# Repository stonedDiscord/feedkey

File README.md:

Replacement PCB for the Zebra GK420 label printers.

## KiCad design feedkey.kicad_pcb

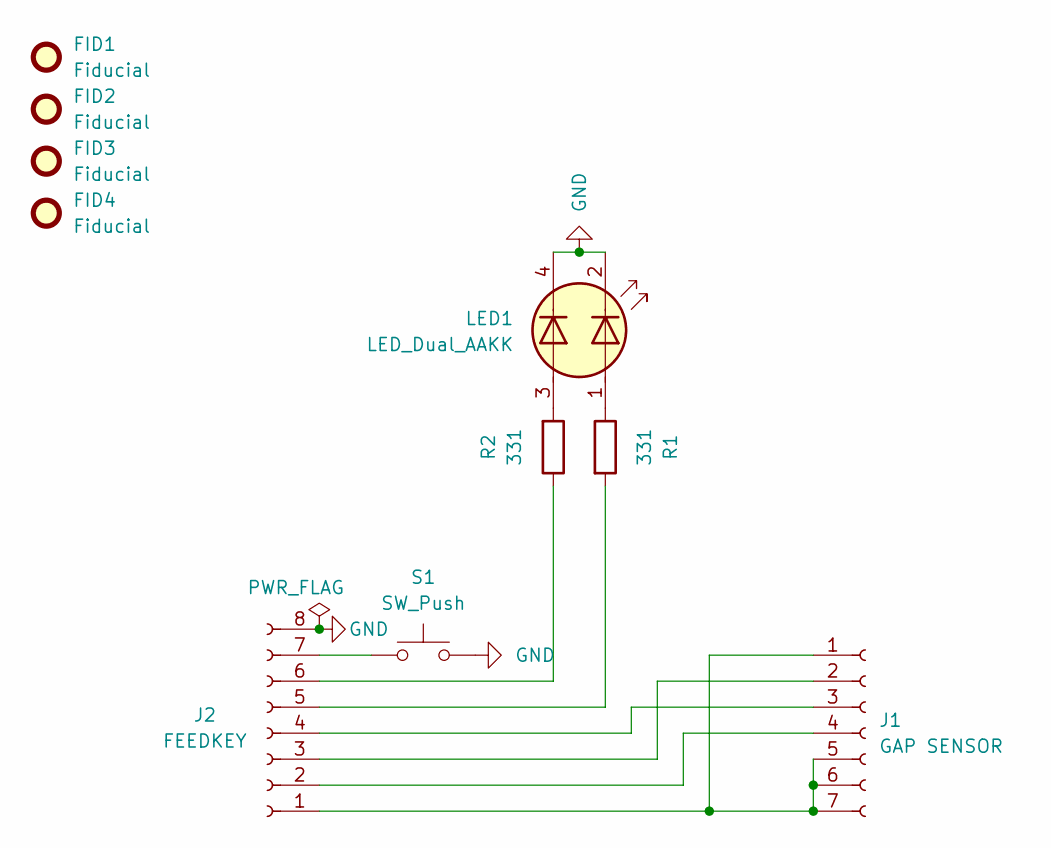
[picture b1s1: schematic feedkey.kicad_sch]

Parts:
FID1, FID2, FID3, FID4: Fiducial; Fiducial_1.5mm_Mask3mm
J1: GAP SENSOR; JST_GH_BM07B-GHS-TBT_1x07-1MP_P1.25mm_Vertical
J2: FEEDKEY; JST_GH_BM08B-GHS-TBT_1x08-1MP_P1.25mm_Vertical
LED1: LED_Dual_AAKK; LED_Kingbright_KPBD-3224
R1, R2: 331; LED_0805_2012Metric
S1: SW_Push; SW_Push_1P1T_NO_6x6mm_H9.5mm

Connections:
GND: J2.8, LED1.2 (K1), LED1.4 (K2), S1.2
unnamed: J1.1, J1.5, J1.6, J1.7, J2.1
unnamed: J1.2, J2.3
unnamed: J1.3, J2.4
unnamed: J1.4, J2.2
unnamed: J2.5, R1.2
unnamed: J2.6, R2.1
unnamed: J2.7, S1.1
unnamed: LED1.1 (A1), R1.1
unnamed: LED1.3 (A2), R2.2

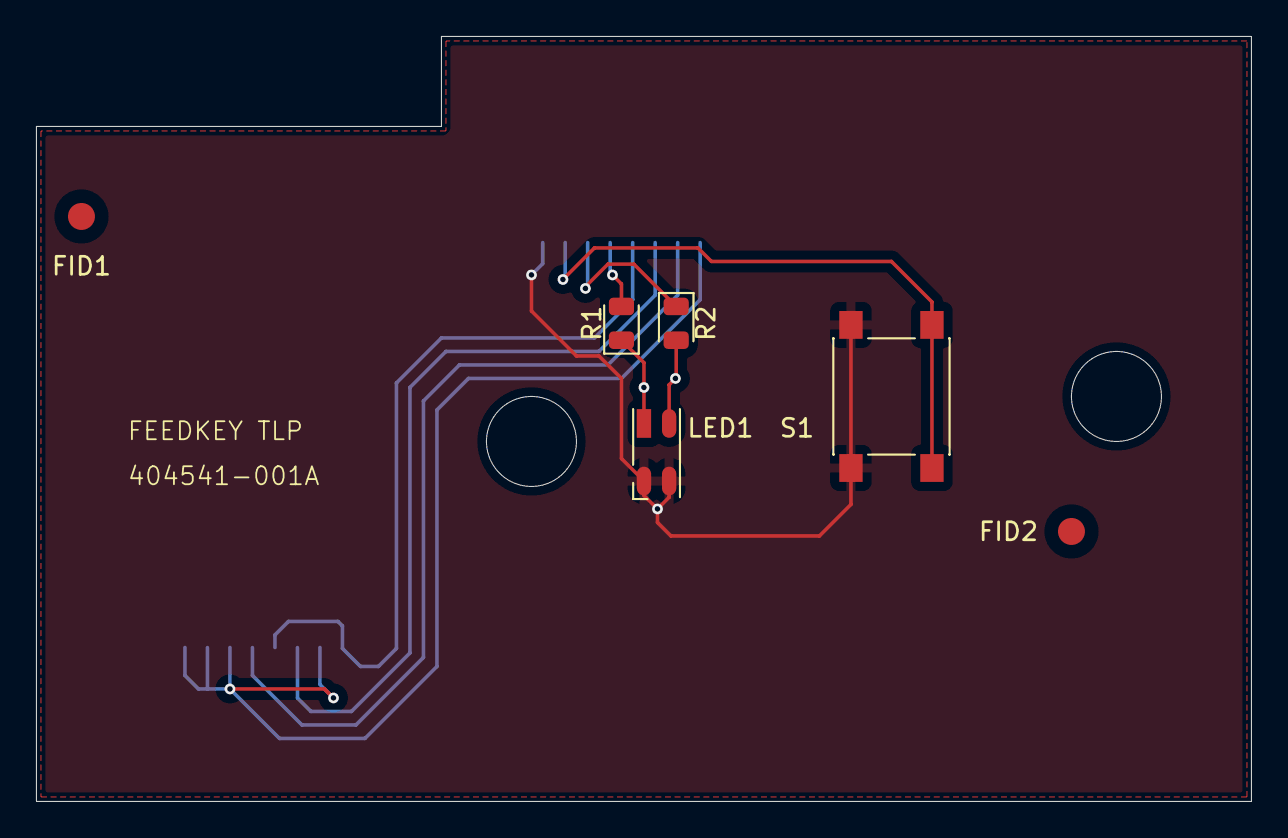
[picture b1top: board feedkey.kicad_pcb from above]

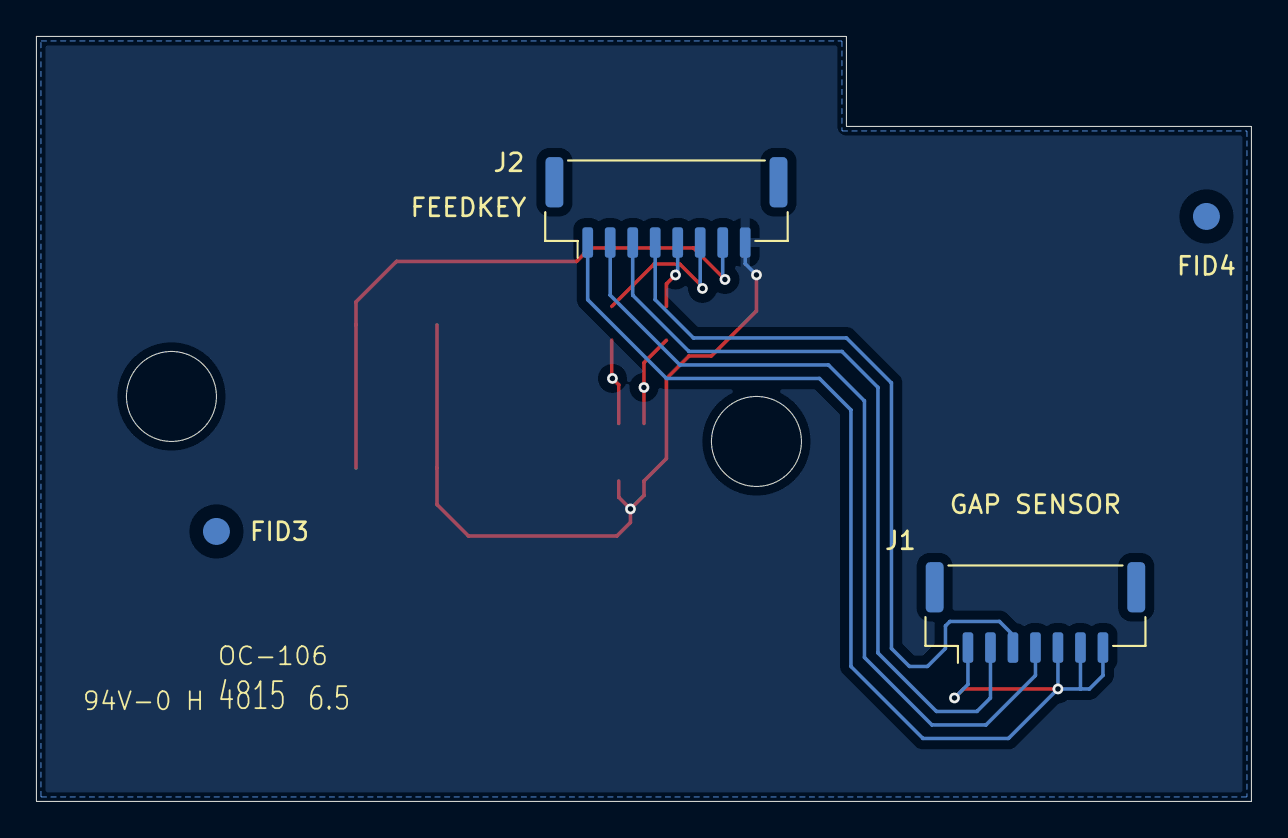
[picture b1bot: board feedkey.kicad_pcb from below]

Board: 2 copper layers, 67.5 x 42.5 mm, 10 parts (4 on the bottom side), 10 nets.
